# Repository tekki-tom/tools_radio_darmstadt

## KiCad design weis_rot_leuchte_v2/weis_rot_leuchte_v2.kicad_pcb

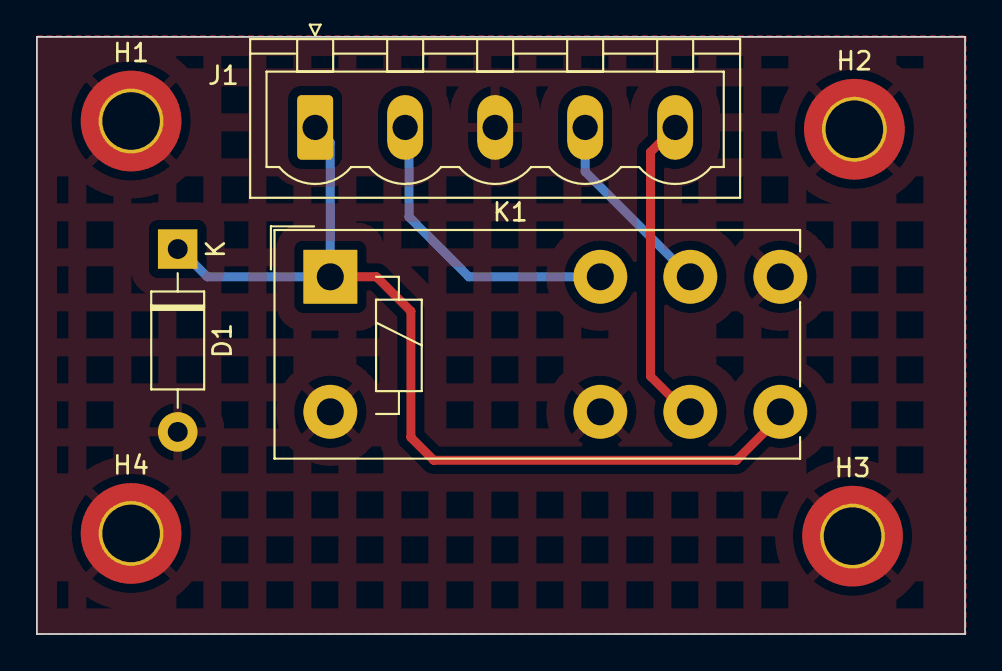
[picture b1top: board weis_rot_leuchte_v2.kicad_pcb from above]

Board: 2 copper layers, 51.6 x 33.2 mm, 7 parts (0 on the bottom side), 5 nets.

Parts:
D1: 1N4001; D_DO-41_SOD81_P10.16mm_Horizontal
H1, H2, H3, H4: MountingHole_Pad; MountingHole_3.2mm_M3_DIN965_Pad_TopBottom
J1: Conn_01x05; PhoenixContact_MSTBVA_2,5_5-G_1x05_P5.00mm_Vertical
K1: FINDER-40.52; Relay_DPDT_Finder_40.52

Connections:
/con_a: J1.4, K1.11
/con_b: J1.5, K1.21
/r_on: J1.2, K1.12
/w_on: D1.1 (K), J1.1, K1.24, K1.A1
GND: D1.2 (A), H1.1, H2.1, H3.1, H4.1, J1.3, K1.14, K1.22, K1.A2

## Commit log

2023-03-19 erster import
